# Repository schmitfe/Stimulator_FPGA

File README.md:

# Stimulator_FPGA
Control of Stimulator with FPGA to speed up data transmission

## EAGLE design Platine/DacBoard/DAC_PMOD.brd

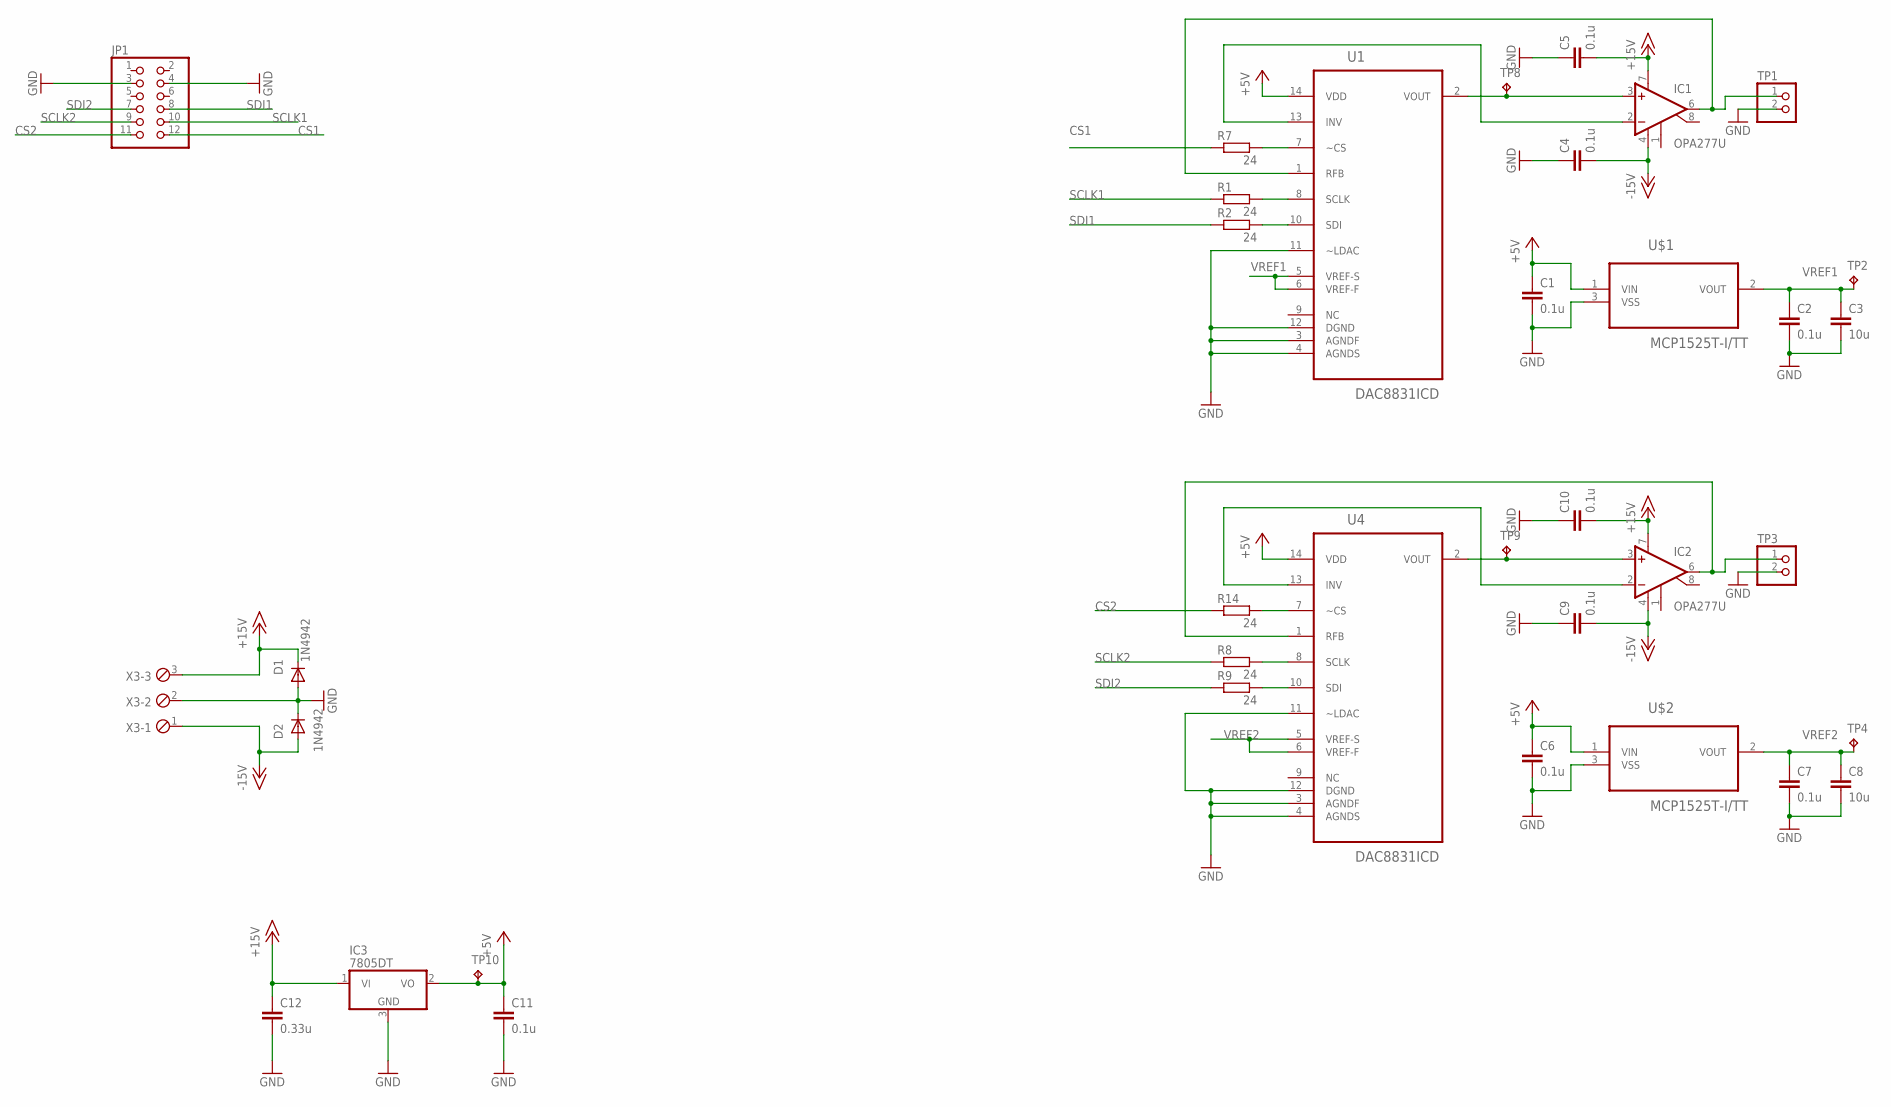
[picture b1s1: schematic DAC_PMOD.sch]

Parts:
C1, C2, C4, C5, C6, C7, C9, C10, C11: 0.1u; C0603
C3, C8: 10u; C0603
C12: 0.33u; C0603
D1, D2: 1N4942; DO41-10
IC1, IC2: OPA277U; SO08
IC3: 7805DT; TO252
JP1: PINHD-2X6/90; 2X06/90
R1, R2, R7, R8, R9, R14: 24; R0603
TP1, TP3: PINHD-1X2; 1X02
TP2, TP4, TP8, TP9, TP10: TPB1,27; B1,27
U1, U4: DAC8831ICD; SOIC127P600X175-14N
U$1, U$2: MCP1525T-I/TT; SOT96P237X112-3N
X3: MPT3; 3POL254

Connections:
+5V: C1.1, C6.1, C11.1, IC3.2 (VO), TP10.TP, U1.14 (VDD), U4.14 (VDD), U$1.1 (VIN), U$2.1 (VIN)
+15V: C5.2, C10.2, C12.1, D1.C, IC1.7 (V+), IC2.7 (V+), IC3.1 (VI), X3.3
-15V: C4.2, C9.2, D2.A, IC1.4 (V-), IC2.4 (V-), X3.1
CS1: JP1.12, R7.1
CS2: JP1.11, R14.1
GND: C1.2, C2.2, C3.2, C4.1, C5.1, C6.2, C7.2, C8.2, C9.1, C10.1, C11.2, C12.2, D1.A, D2.C, IC3.3 (GND), JP1.3, JP1.4, TP1.2, TP3.2, U1.3 (AGNDF), U1.4 (AGNDS), U1.11 (~LDAC), U1.12 (DGND), U4.3 (AGNDF), U4.4 (AGNDS), U4.11 (~LDAC), U4.12 (DGND), U$1.3 (VSS), U$2.3 (VSS), X3.2
unnamed: IC1.3 (+IN), TP8.TP, U1.2 (VOUT)
unnamed: IC1.2 (-IN), U1.13 (INV)
unnamed: IC1.6 (OUT), TP1.1, U1.1 (RFB)
unnamed: R1.2, U1.8 (SCLK)
unnamed: R2.2, U1.10 (SDI)
unnamed: IC2.3 (+IN), TP9.TP, U4.2 (VOUT)
unnamed: R7.2, U1.7 (~CS)
unnamed: IC2.2 (-IN), U4.13 (INV)
unnamed: IC2.6 (OUT), TP3.1, U4.1 (RFB)
unnamed: R8.2, U4.8 (SCLK)
unnamed: R9.2, U4.10 (SDI)
unnamed: R14.2, U4.7 (~CS)
SCLK1: JP1.10, R1.1
SCLK2: JP1.9, R8.1
SDI1: JP1.8, R2.1
SDI2: JP1.7, R9.1
VREF1: C2.1, C3.1, TP2.TP, U1.5 (VREF-S), U1.6 (VREF-F), U$1.2 (VOUT)
VREF2: C7.1, C8.1, TP4.TP, U4.5 (VREF-S), U4.6 (VREF-F), U$2.2 (VOUT)

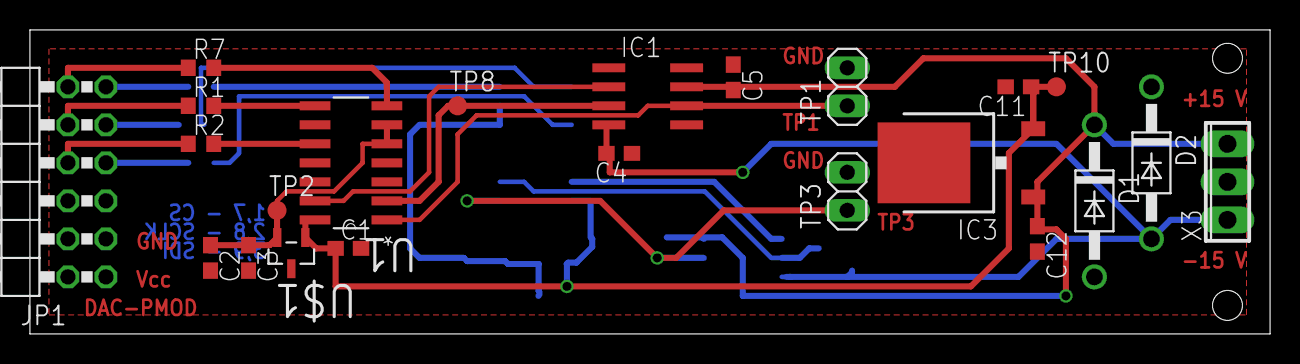
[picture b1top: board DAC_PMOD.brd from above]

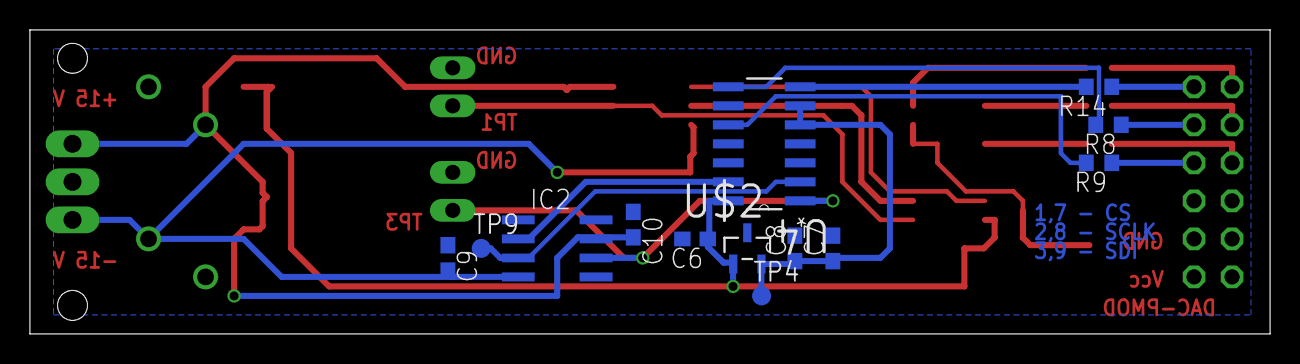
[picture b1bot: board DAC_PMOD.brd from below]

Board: 2 copper layers, 82.9 x 20.3 mm, 36 parts (13 on the bottom side), 24 nets.

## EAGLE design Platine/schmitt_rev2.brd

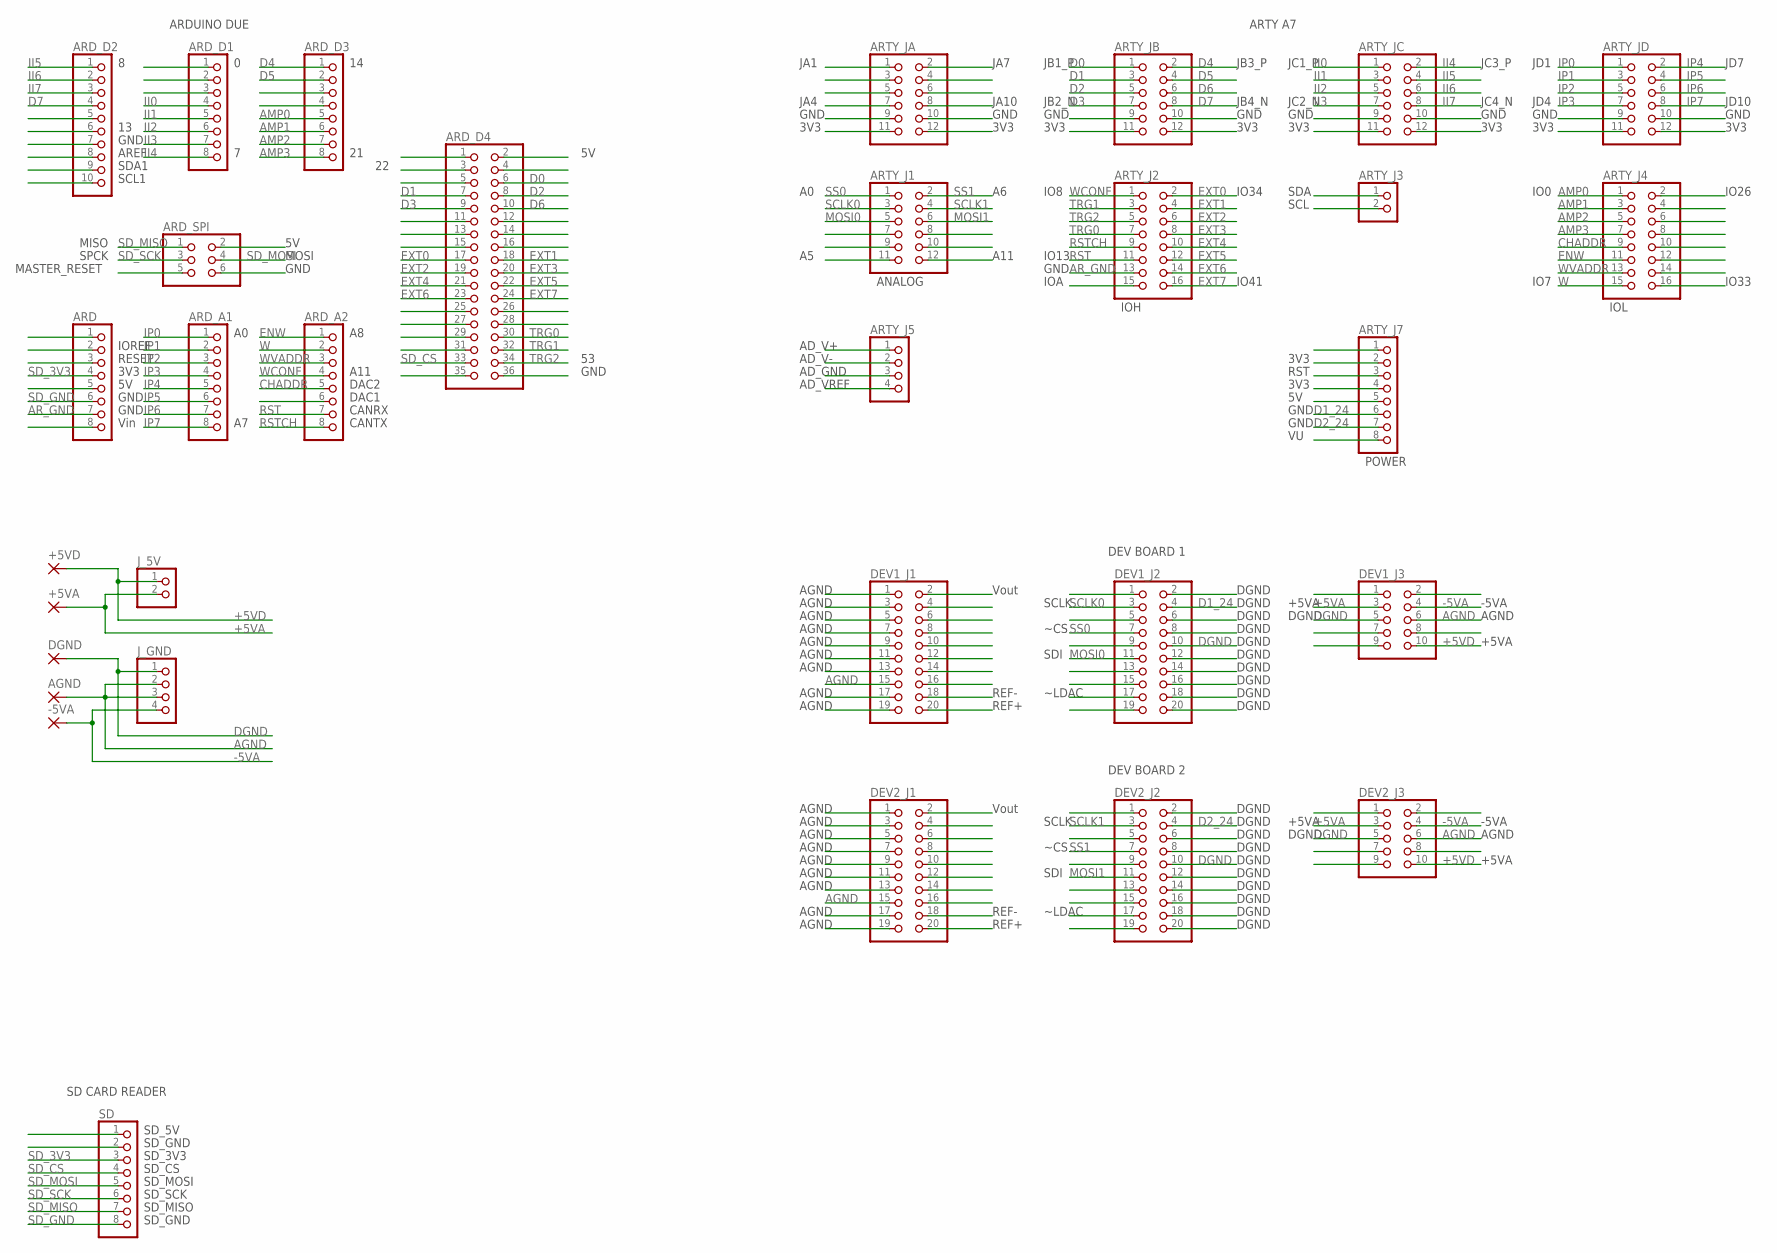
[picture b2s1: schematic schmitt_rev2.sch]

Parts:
+5VA, +5VD: 2,15/1,0
-5VA: 2,15/1,0
AGND: 2,15/1,0
ARD: PINHD-1X8; 1X08
ARD_A1, ARD_A2: PINHD-1X8; 1X08
ARD_D1, ARD_D3: PINHD-1X8; 1X08
ARD_D2: PINHD-1X10; 1X10
ARD_D4: PINHD-2X18; 2X18
ARD_SPI: PINHD-2X3; 2X03
ARTY_J1: PINHD-2X6; 2X06
ARTY_J2, ARTY_J4: PINHD-2X8; 2X08
ARTY_J3: PINHD-1X2; 1X02
ARTY_J5: PINHD-1X4; 1X04
ARTY_J7: PINHD-1X8; 1X08
ARTY_JA: PINHD-2X6; 2X06
ARTY_JB: PINHD-2X6; 2X06
ARTY_JC: PINHD-2X6; 2X06
ARTY_JD: PINHD-2X6; 2X06
DEV1_J1, DEV1_J2, DEV2_J1, DEV2_J2: PINHD-2X10; 2X10
DEV1_J3, DEV2_J3: PINHD-2X5; 2X05
DGND: 2,15/1,0
J_5V: PINHD-1X2; 1X02
J_GND: PINHD-1X4; 1X04
SD: PINHD-1X8; 1X08

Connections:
+5VA: +5VA.1, DEV1_J3.3, DEV2_J3.3, J_5V.2
+5VD: +5VD.1, DEV1_J3.10, DEV2_J3.10, J_5V.1
-5VA: -5VA.1, DEV1_J3.4, DEV2_J3.4, J_GND.4
AGND: AGND.1, DEV1_J1.15, DEV1_J3.6, DEV2_J1.15, DEV2_J3.6, J_GND.2, J_GND.3
AMP0: ARD_D3.5, ARTY_J4.1
AMP1: ARD_D3.6, ARTY_J4.3
AMP2: ARD_D3.7, ARTY_J4.5
AMP3: ARD_D3.8, ARTY_J4.7
ARD_SPI: ARD_SPI.6
AR_GND: ARD.7, ARTY_J2.13
CHADDR: ARD_A2.5, ARTY_J4.9
D0: ARD_D4.6, ARTY_JB.1
D1: ARD_D4.7, ARTY_JB.3
D1_24: ARTY_J7.6, DEV1_J2.4
D2: ARD_D4.8, ARTY_JB.5
D2_24: ARTY_J7.7, DEV2_J2.4
D3: ARD_D4.9, ARTY_JB.7
D4: ARD_D3.1, ARTY_JB.2
D5: ARD_D3.2, ARTY_JB.4
D6: ARD_D4.10, ARTY_JB.6
D7: ARD_D2.4, ARTY_JB.8
DGND: DEV1_J2.10, DEV1_J3.5, DEV2_J2.10, DEV2_J3.5, DGND.1, J_GND.1
ENW: ARD_A2.1, ARTY_J4.11
EXT0: ARD_D4.17, ARTY_J2.2
EXT1: ARD_D4.18, ARTY_J2.4
EXT2: ARD_D4.19, ARTY_J2.6
EXT3: ARD_D4.20, ARTY_J2.8
EXT4: ARD_D4.21, ARTY_J2.10
EXT5: ARD_D4.22, ARTY_J2.12
EXT6: ARD_D4.23, ARTY_J2.14
EXT7: ARD_D4.24, ARTY_J2.16
II0: ARD_D1.4, ARTY_JC.1
II1: ARD_D1.5, ARTY_JC.3
II2: ARD_D1.6, ARTY_JC.5
II3: ARD_D1.7, ARTY_JC.7
II4: ARD_D1.8, ARTY_JC.2
II5: ARD_D2.1, ARTY_JC.4
II6: ARD_D2.2, ARTY_JC.6
II7: ARD_D2.3, ARTY_JC.8
IP0: ARD_A1.1, ARTY_JD.1
IP1: ARD_A1.2, ARTY_JD.3
IP2: ARD_A1.3, ARTY_JD.5
IP3: ARD_A1.4, ARTY_JD.7
IP4: ARD_A1.5, ARTY_JD.2
IP5: ARD_A1.6, ARTY_JD.4
IP6: ARD_A1.7, ARTY_JD.6
IP7: ARD_A1.8, ARTY_JD.8
MOSI0: ARTY_J1.5, DEV1_J2.11
MOSI1: ARTY_J1.6, DEV2_J2.11
RST: ARD_A2.7, ARTY_J2.11
RSTCH: ARD_A2.8, ARTY_J2.9
SCLK0: ARTY_J1.3, DEV1_J2.3
SCLK1: ARTY_J1.4, DEV2_J2.3
SD_3V3: ARD.4, SD.3
SD_CS: ARD_D4.33, SD.4
SD_GND: ARD.6, SD.8
SD_MISO: ARD_SPI.1, SD.7
SD_MOSI: ARD_SPI.4, SD.5
SD_SCK: ARD_SPI.3, SD.6
SS0: ARTY_J1.1, DEV1_J2.7
SS1: ARTY_J1.2, DEV2_J2.7
TRG0: ARD_D4.30, ARTY_J2.7
TRG1: ARD_D4.32, ARTY_J2.3
TRG2: ARD_D4.34, ARTY_J2.5
W: ARD_A2.2, ARTY_J4.15
WCONF: ARD_A2.4, ARTY_J2.1
WVADDR: ARD_A2.3, ARTY_J4.13

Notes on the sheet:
SD CARD READER
SD_GND
SD_5V
SD_3V3
SD_CS
SD_MOSI
SD_SCK
SD_MISO
SCL1
SDA1
AREF
GND
CANRX
CANTX
DAC1
DAC2
A11
Vin
3V3
RESET
IOREF
MISO
SPCK
MASTER_RESET
MOSI
ARDUINO DUE
ARTY A7
JA1
JA4
JA7
JA10
JB1_P
JB2_N
JB4_N
JB3_P
JC1_P
JC2_N
JC3_P
JC4_N
JD1

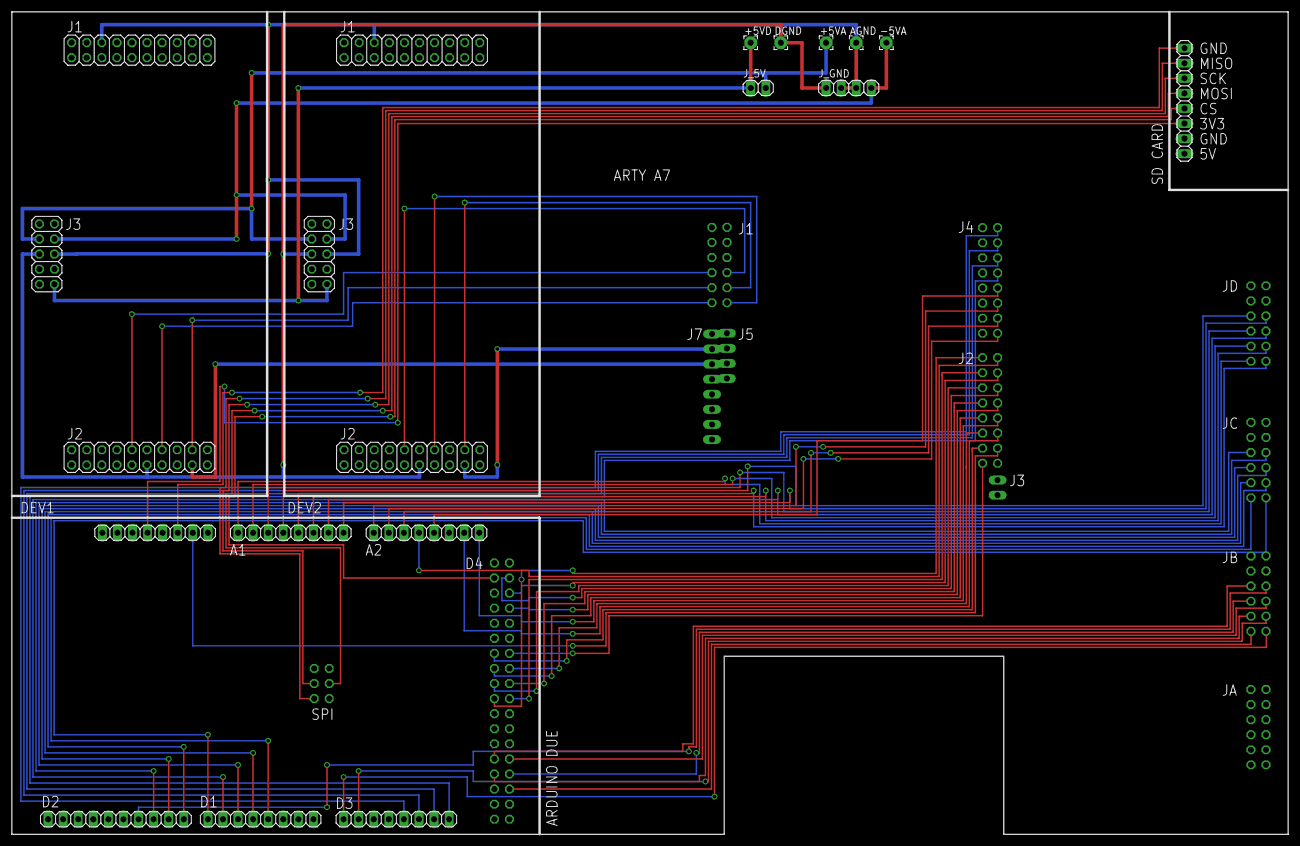
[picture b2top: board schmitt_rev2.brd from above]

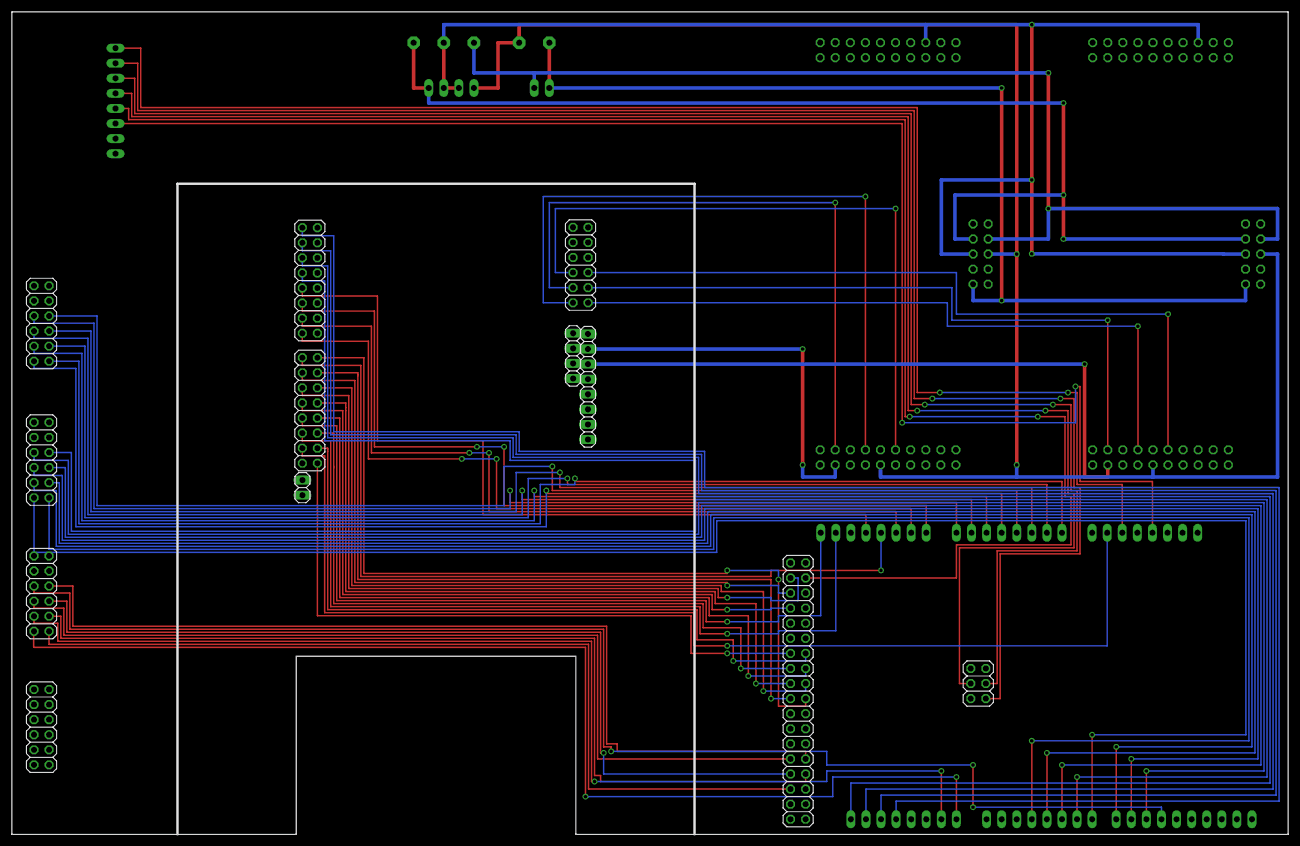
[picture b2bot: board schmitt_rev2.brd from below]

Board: 2 copper layers, 215.0 x 138.6 mm, 32 parts (12 on the bottom side), 66 nets.

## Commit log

2019-07-29 Updated Simulation
    After Starting to write one has to wait for several periods
2019-07-30 Init Memory at start.
2019-07-30 Add Logic to toggle between WF1 and WF2 to generate full configurable Waveform
2019-07-30 Working Changes
2019-08-01 Update DataSource.vhd
    Added Delays:
    Inter Period
    Inter Interval
    Added Divider for Waveform
2019-08-01 Updated to test new delays
2019-08-05 Added register tx_reg2 to debug output
2019-08-05 Updated Testfiles to test trig
2019-08-05 Added Gain and Offset
2019-08-05 Load first dataword after readcounter reset
2019-08-07 Added Top-entity with configurable number of channels
2019-08-08 Update DataSource.vhd
    Reduced code complexety:
    - one timer
    - States for WF1 and WF2
2019-08-08 Bugfic
    Bugfix of Interperiod Delay
2019-09-14 Includes Arduino program as interface
2019-09-29 Upload of whole Project
2019-11-09 Stand 11.09.2019
2019-11-17 Added redundancy to Write and ChanAdress
2019-11-17 Names adjusted to fit each other
2019-11-17 Added Arduino Due pinout
2019-11-23 Added Comments
2019-11-23 Remove Zero Padding in WF1
2019-11-24 Upload DAC board
2019-11-24 Moved to subfolder
2019-11-24 Commit from 24.11
2019-12-14 Adjusted Pins and Manual to Board
2019-12-31 Changed wiring allows 50 MHz SD speed
